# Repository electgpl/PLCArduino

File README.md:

# PLC Arduino NANO v1 

Este es un PLC de openHard diseñado en base al microcontrolador AVR linea MEGA compatible ArduinoIDE y ArduinoNANO

  - Core AVR - **ARDUINO NANO (Versión CH340)**
  - Bootloader UART Arduino Compatible
  - USB Programming firmware
  - USB Serial Terminal/Debug
  - 4 Salidas contacto seco doble inversora 12Vdc 24Vdc 220Vac
  - 4 Entradas Digitales optoacopladas 0-10V 0-12V 0-24V 
  - 3 Entradas Analógicas Aisladas de 0-10V
  - Fuente de alimentación integrada

## Lenguajes Compatibles

  - C
  - C++
  - Basic
  - Ensamblador
  - Ladder
  - y mas...
  
## Diseño y Desarrollo

> Diseñado en dos capas con componentes THT para facilitar
> la integración al alumno, el desarrollo del PCB en el hogar y mantener
> el menor costo posible.
>                           
> PCB creado en [PCBWay].
> Diseño realizado en [Eagle].

### Instalación

Todos los archivos se encuentran disponibles en este repositorio, diagramas, pcb, etc...

### Pendientes

 - Migración del hardware AVR MEGA Compatible.
 - Incorporación de nuevos puertos de comunicación CAN, 232, 485, ethernet, BT, WiFi (Requiere un PCB de mayores dimensiones, miltilayers y tecnología SMT)
 - Mejoras en inmunidad al ruido con incorporación de componentes dedicados, MOV, TVS, PLCC, EMC, BEADS CORE
 - Mejora en la performance de la fuente utilizando un DCDC Sepic o Buck/Boost
 - Aumento de canales de entrada y salida
 - Incorporación de entrada 4-20mA

License
----

MIT

**Free Software, Hell Yeah!**

[PCBWay]: <https://www.pcbway.com/>
[Eagle]: <https://www.autodesk.com/products/eagle/overview>

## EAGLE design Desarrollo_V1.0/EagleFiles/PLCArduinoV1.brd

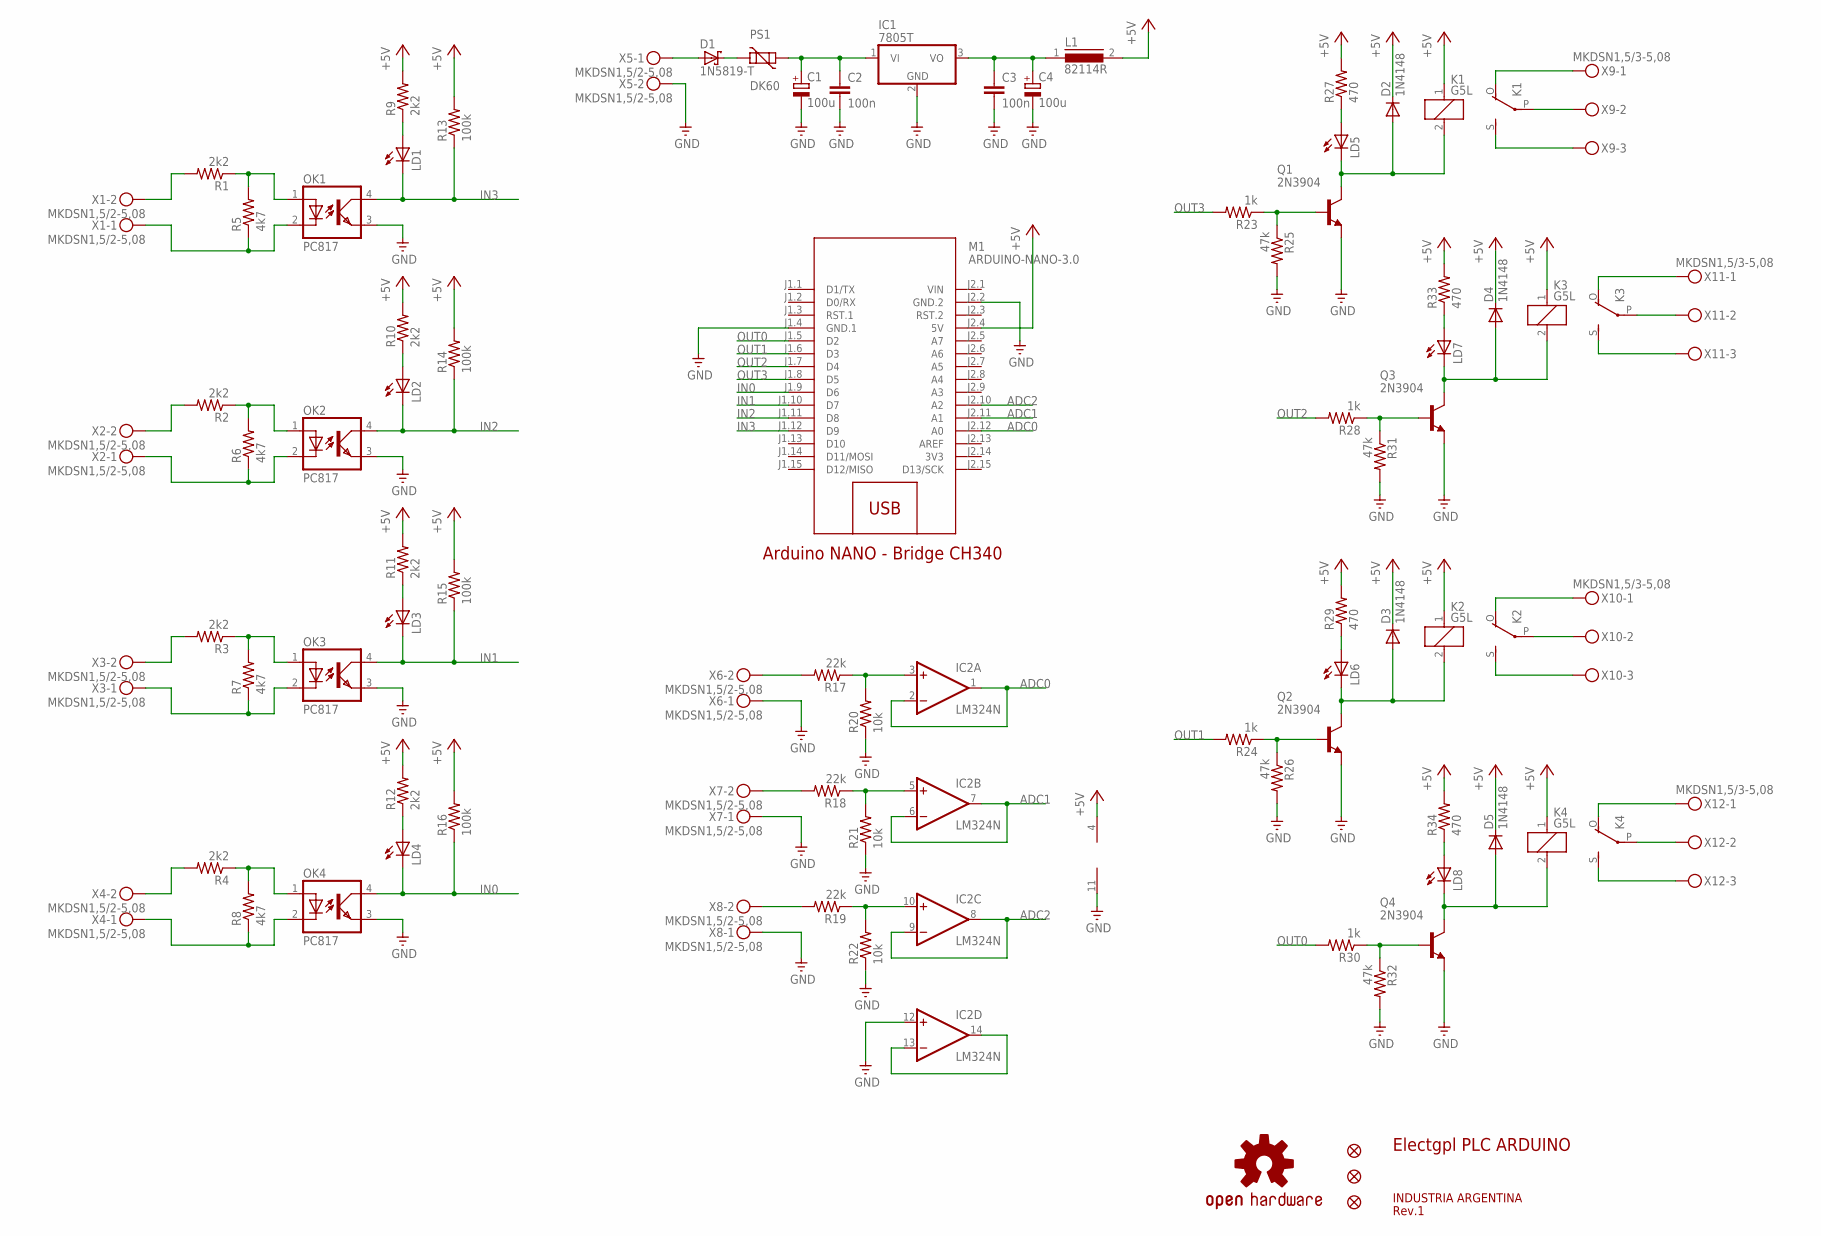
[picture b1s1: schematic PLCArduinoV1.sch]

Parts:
C1, C4: 100u; E3,5-8
C2, C3: 100n; C050-024X044
D1: 1N5819-T; DO41-7.6
D2, D3, D4, D5: 1N4148; DO35-10
IC1: 7805T; TO220H
IC2: LM324N; DIL14
JP1, JP2, JP3: FIDUCIAL1X2.5; FIDUCIAL-1X2.5
K1, K2, K3, K4: G5L; G5LE
L1: 82114R
LD1, LD2, LD3, LD4, LD5, LD6, LD7, LD8: LED3MM
M1: ARDUINO-NANO-3.0
OK1, OK2, OK3, OK4: PC817; DIL04
PS1: DK60; SO5K11
Q1, Q2, Q3, Q4: 2N3904; TO92
R1, R2, R3, R4, R9, R10, R11, R12: 2k2; 0204/5
R5, R6, R7, R8: 4k7; 0204/5
R13, R14, R15, R16: 100k; 0204/5
R17, R18, R19: 22k; 0204/5
R20, R21, R22: 10k; 0204/5
R23, R24, R28, R30: 1k; 0204/5
R25, R26, R31, R32: 47k; 0204/5
R27, R29, R33, R34: 470; 0204/5
U1: OSHW-LOGOM; OSHW-LOGO-M
X1, X2, X3, X4, X5, X6, X7, X8: MKDSN1,5/2-5,08
X9, X10, X11, X12: MKDSN1,5/3-5,08

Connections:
3V3: M1.J2.14 (3V3)
+5V: D2.C, D3.C, D4.C, D5.C, IC2.4 (V+), K1.1, K2.1, K3.1, K4.1, L1.2, M1.J2.4 (5V), R9.2, R10.2, R11.2, R12.2, R13.2, R14.2, R15.2, R16.2, R27.2, R29.2, R33.2, R34.2
ADC0: IC2.1 (OUT), IC2.2 (-IN), M1.J2.12 (A0)
ADC1: IC2.6 (-IN), IC2.7 (OUT), M1.J2.11 (A1)
ADC2: IC2.8 (OUT), IC2.9 (-IN), M1.J2.10 (A2)
GND: C1.-, C2.2, C3.2, C4.-, IC1.2 (GND), IC2.11 (V-), IC2.12 (+IN), M1.J1.4 (GND.1), M1.J2.2 (GND.2), OK1.3 (EMIT), OK2.3 (EMIT), OK3.3 (EMIT), OK4.3 (EMIT), Q1.3 (E), Q2.3 (E), Q3.3 (E), Q4.3 (E), R20.1, R21.1, R22.1, R25.2, R26.2, R31.2, R32.2, X5.2, X6.1, X7.1, X8.1
IN0: LD4.K (C), M1.J1.9 (D6), OK4.4 (COL), R16.1
IN1: LD3.K (C), M1.J1.10 (D7), OK3.4 (COL), R15.1
IN2: LD2.K (C), M1.J1.11 (D8), OK2.4 (COL), R14.1
IN3: LD1.K (C), M1.J1.12 (D9), OK1.4 (COL), R13.1
unnamed: LD5.A, R27.1
unnamed: D2.A, K1.2, LD5.K (C), Q1.1 (C)
unnamed: Q1.2 (B), R23.1, R25.1
unnamed: K1.P, X9.2
unnamed: K1.O, X9.1
unnamed: K1.S, X9.3
unnamed: LD7.A, R33.1
unnamed: D4.A, K3.2, LD7.K (C), Q3.1 (C)
unnamed: Q3.2 (B), R28.1, R31.1
unnamed: K3.P, X11.2
unnamed: K3.O, X11.1
unnamed: K3.S, X11.3
unnamed: LD6.A, R29.1
unnamed: D3.A, K2.2, LD6.K (C), Q2.1 (C)
unnamed: Q2.2 (B), R24.1, R26.1
unnamed: K2.P, X10.2
unnamed: K2.O, X10.1
unnamed: K2.S, X10.3
unnamed: LD8.A, R34.1
unnamed: D5.A, K4.2, LD8.K (C), Q4.1 (C)
unnamed: Q4.2 (B), R30.1, R32.1
unnamed: K4.P, X12.2
unnamed: K4.O, X12.1
unnamed: K4.S, X12.3
unnamed: OK1.1 (A), R1.1, R5.2
unnamed: OK1.2 (C), R5.1, X1.1
unnamed: R17.2, X6.2
unnamed: R18.2, X7.2
unnamed: LD1.A, R9.1
unnamed: R1.2, X1.2
unnamed: R19.2, X8.2
unnamed: OK2.1 (A), R2.1, R6.2
unnamed: OK2.2 (C), R6.1, X2.1
unnamed: LD2.A, R10.1
unnamed: R2.2, X2.2
unnamed: OK3.1 (A), R3.1, R7.2
unnamed: OK3.2 (C), R7.1, X3.1
unnamed: D1.A, X5.1
unnamed: LD3.A, R11.1
unnamed: R3.2, X3.2
unnamed: OK4.1 (A), R4.1, R8.2
unnamed: OK4.2 (C), R8.1, X4.1
unnamed: D1.C, PS1.2
unnamed: LD4.A, R12.1
unnamed: R4.2, X4.2
unnamed: C1.+, C2.1, IC1.1 (VI), PS1.1
unnamed: C3.1, C4.+, IC1.3 (VO), L1.1
unnamed: IC2.3 (+IN), R17.1, R20.2
unnamed: IC2.5 (+IN), R18.1, R21.2
unnamed: IC2.10 (+IN), R19.1, R22.2
unnamed: IC2.13 (-IN), IC2.14 (OUT)
OUT0: M1.J1.5 (D2), R30.2
OUT1: M1.J1.6 (D3), R24.2
OUT2: M1.J1.7 (D4), R28.2
OUT3: M1.J1.8 (D5), R23.2
VIN: M1.J2.1 (VIN)

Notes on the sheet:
Electgpl PLC ARDUINO
INDUSTRIA ARGENTINA
Rev.1
Arduino NANO - Bridge CH340

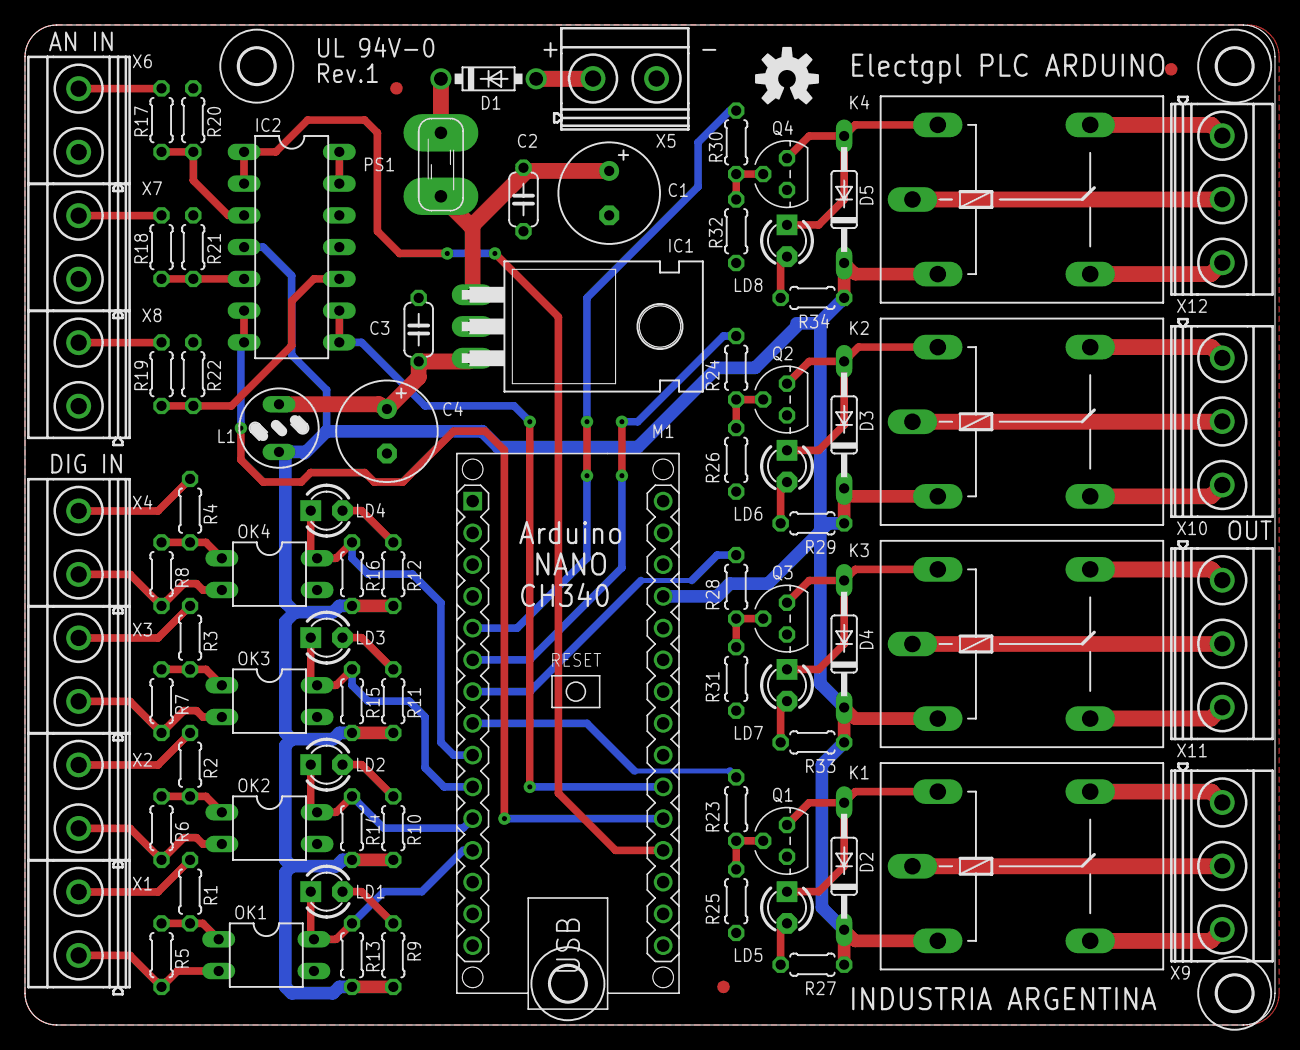
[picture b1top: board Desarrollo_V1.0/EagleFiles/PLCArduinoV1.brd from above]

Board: 2 copper layers, 100.0 x 80.0 mm, 88 parts (0 on the bottom side), 64 nets.

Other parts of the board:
U$2, U$3, U$4, U$5: 2,8

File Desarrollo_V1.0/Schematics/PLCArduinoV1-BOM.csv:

"Qty";"Value";"Device";"Package";"Parts";"Description";"SPICEPREFIX";
"8";"";"LED3MM";"LED3MM";"LD1, LD2, LD3, LD4, LD5, LD6, LD7, LD8";"LED";"";
"4";"100k";"R-US_0204/5";"0204/5";"R13, R14, R15, R16";"RESISTOR, American symbol";"R";
"2";"100n";"C-EU050-024X044";"C050-024X044";"C2, C3";"CAPACITOR, European symbol";"C";
"2";"100u";"CPOL-EUE3.5-8";"E3,5-8";"C1, C4";"POLARIZED CAPACITOR, European symbol";"C";
"3";"10k";"R-US_0204/5";"0204/5";"R20, R21, R22";"RESISTOR, American symbol";"R";
"4";"1N4148";"1N4148";"DO35-10";"D2, D3, D4, D5";"DIODE";"";
"1";"1N5819-T";"1N5819-T";"DO41-7.6";"D1";"1.0A SCHOTTKY BARRIER RECTIFIER";"";
"4";"1k";"R-US_0204/5";"0204/5";"R23, R24, R28, R30";"RESISTOR, American symbol";"R";
"3";"22k";"R-US_0204/5";"0204/5";"R17, R18, R19";"RESISTOR, American symbol";"R";
"4";"2N3904";"2N3904";"TO92";"Q1, Q2, Q3, Q4";"NPN Transistor";"";
"8";"2k2";"R-US_0204/5";"0204/5";"R1, R2, R3, R4, R9, R10, R11, R12";"RESISTOR, American symbol";"R";
"4";"470";"R-US_0204/5";"0204/5";"R27, R29, R33, R34";"RESISTOR, American symbol";"R";
"4";"47k";"R-US_0204/5";"0204/5";"R25, R26, R31, R32";"RESISTOR, American symbol";"R";
"4";"4k7";"R-US_0204/5";"0204/5";"R5, R6, R7, R8";"RESISTOR, American symbol";"R";
"1";"7805T";"7805T";"TO220H";"IC1";"Positive VOLTAGE REGULATOR";"";
"1";"82114R";"82114R";"82114R";"L1";"INDUCTOR";"L";
"1";"ARDUINO-NANO-3.0";"ARDUINO-NANO-3.0";"ARDUINO-NANO-3.0";"M1";"Arduino Nano 3.0 and compatible devices";"";
"1";"DK60";"POLYSWITCH5MM";"SO5K11";"PS1";"";"";
"3";"FIDUCIAL1X2.5";"FIDUCIAL1X2.5";"FIDUCIAL-1X2.5";"JP1, JP2, JP3";"Fiducial Alignment Points";"";
"4";"G5L";"G5L";"G5LE";"K1, K2, K3, K4";"RELAY";"";
"1";"LM324N";"LM324N";"DIL14";"IC2";"OP AMP";"";
"8";"MKDSN1,5/2-5,08";"MKDSN1,5/2-5,08";"MKDSN1,5/2-5,08";"X1, X2, X3, X4, X5, X6, X7, X8";"MKDSN 1,5/ 2-5,08 Printklemme";"";
"4";"MKDSN1,5/3-5,08";"MKDSN1,5/3-5,08";"MKDSN1,5/3-5,08";"X9, X10, X11, X12";"MKDSN 1,5/ 3-5,08 Printklemme";"";
"1";"OSHW-LOGOM";"OSHW-LOGOM";"OSHW-LOGO-M";"U1";"Open Source Hardware Logo This logo indicates the piece of hardware it is found on incorporates a OSHW license and/or adheres to the definition of open source hardware found here: http://freedomdefined.org/OSHW";"";
"4";"PC817";"PC817";"DIL04";"OK1, OK2, OK3, OK4";"SHARP OPTO COUPLER";"";

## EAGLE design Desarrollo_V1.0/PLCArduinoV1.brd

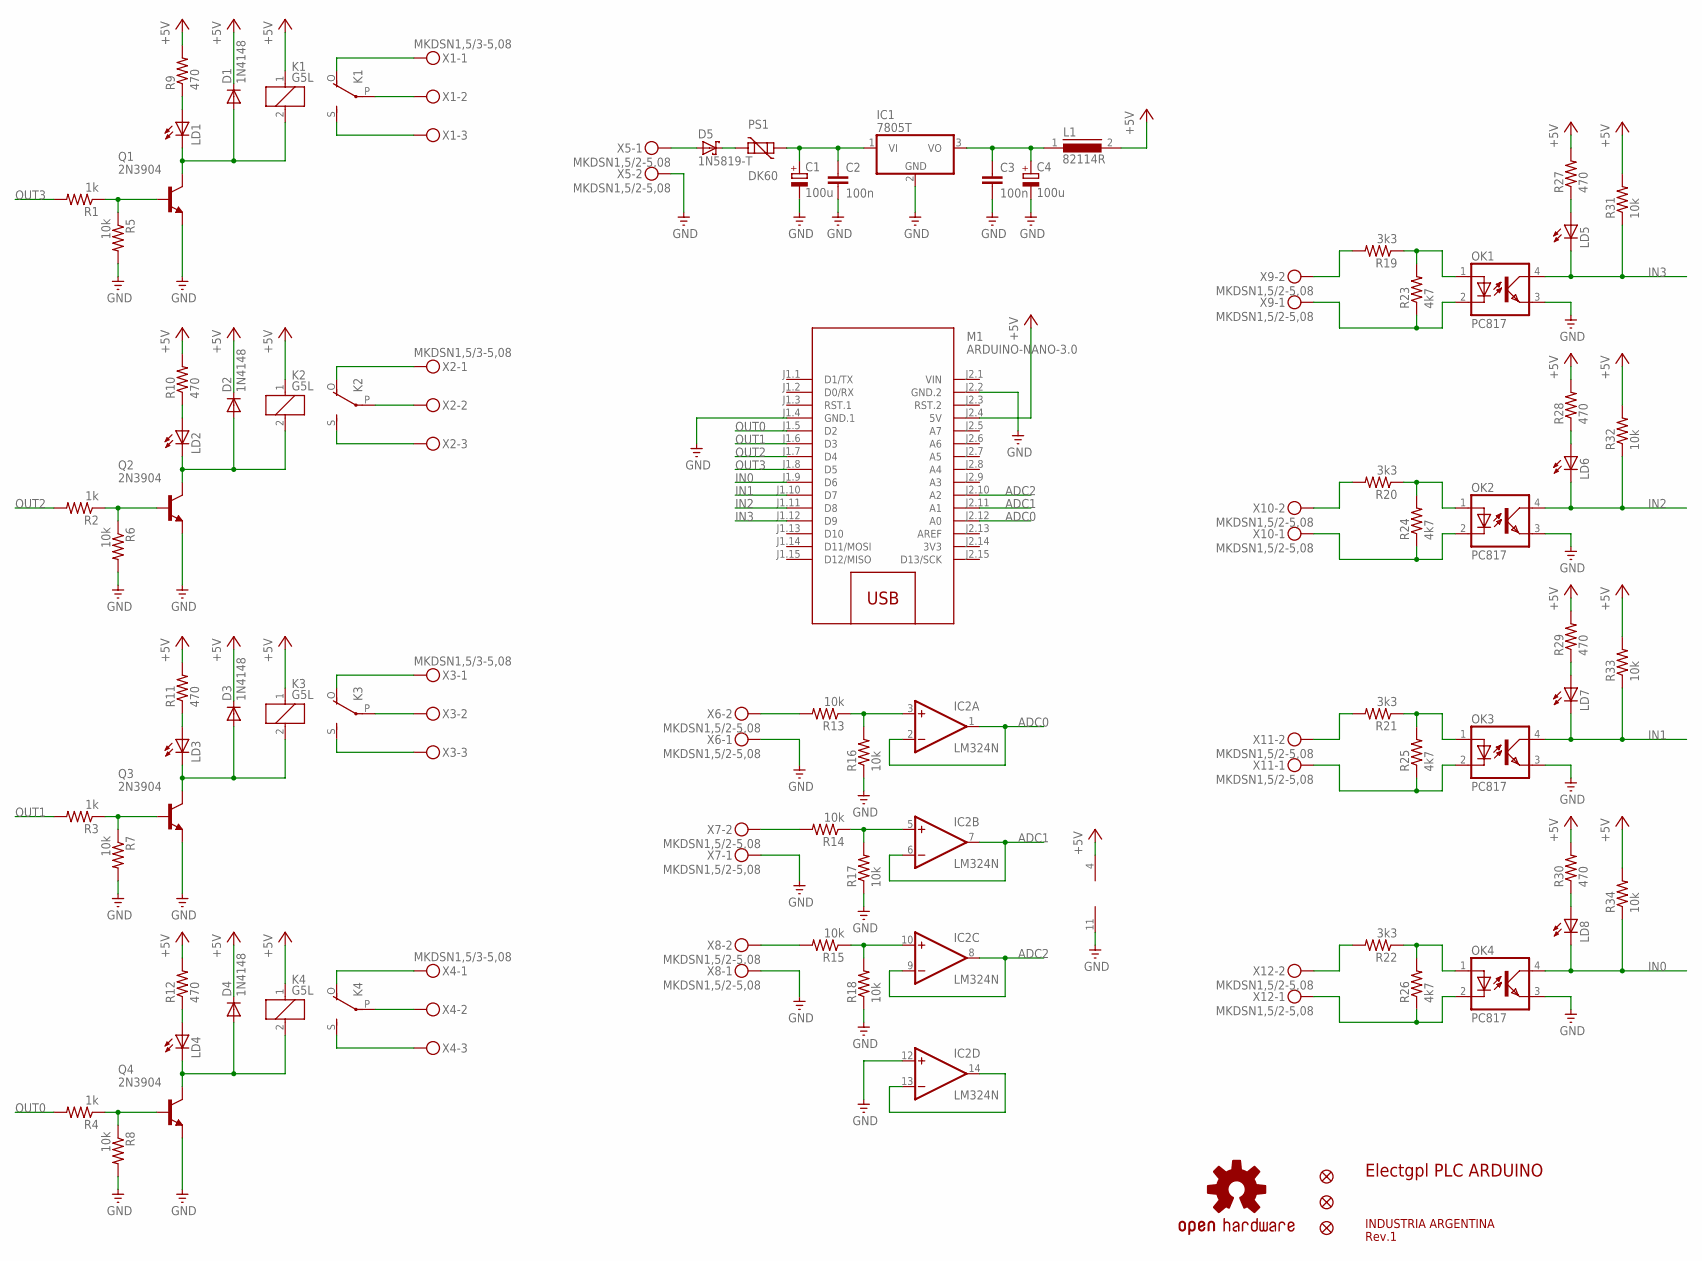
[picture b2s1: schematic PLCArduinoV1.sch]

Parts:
C1, C4: 100u; E3,5-8
C2, C3: 100n; C050-024X044
D1, D2, D3, D4: 1N4148; DO35-10
D5: 1N5819-T; DO41-7.6
IC1: 7805T; TO220H
IC2: LM324N; DIL14
JP1, JP2, JP3: FIDUCIAL1X2.5; FIDUCIAL-1X2.5
K1, K2, K3, K4: G5L; G5LE
L1: 82114R
LD1, LD2, LD3, LD4, LD5, LD6, LD7, LD8: LED3MM
M1: ARDUINO-NANO-3.0
OK1, OK2, OK3, OK4: PC817; DIL04
PS1: DK60; SO5K11
Q1, Q2, Q3, Q4: 2N3904; TO92
R1, R2, R3, R4: 1k; 0204/5
R5, R6, R7, R8, R13, R14, R15, R16, R17, R18, R31, R32, R33, R34: 10k; 0204/5
R9, R10, R11, R12, R27, R28, R29, R30: 470; 0204/5
R19, R20, R21, R22: 3k3; 0204/5
R23, R24, R25, R26: 4k7; 0204/5
U1: OSHW-LOGOM; OSHW-LOGO-M
X1, X2, X3, X4: MKDSN1,5/3-5,08
X5, X6, X7, X8, X9, X10, X11, X12: MKDSN1,5/2-5,08

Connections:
3V3: M1.J2.14 (3V3)
+5V: D1.C, D2.C, D3.C, D4.C, IC2.4 (V+), K1.1, K2.1, K3.1, K4.1, L1.2, M1.J2.4 (5V), R9.2, R10.2, R11.2, R12.2, R27.2, R28.2, R29.2, R30.2, R31.2, R32.2, R33.2, R34.2
ADC0: IC2.1 (OUT), IC2.2 (-IN), M1.J2.12 (A0)
ADC1: IC2.6 (-IN), IC2.7 (OUT), M1.J2.11 (A1)
ADC2: IC2.8 (OUT), IC2.9 (-IN), M1.J2.10 (A2)
GND: C1.-, C2.2, C3.2, C4.-, IC1.2 (GND), IC2.11 (V-), IC2.12 (+IN), M1.J1.4 (GND.1), M1.J2.2 (GND.2), OK1.3 (EMIT), OK2.3 (EMIT), OK3.3 (EMIT), OK4.3 (EMIT), Q1.3 (E), Q2.3 (E), Q3.3 (E), Q4.3 (E), R5.2, R6.2, R7.2, R8.2, R16.1, R17.1, R18.1, X5.2, X6.1, X7.1, X8.1
IN0: LD8.K (C), M1.J1.9 (D6), OK4.4 (COL), R34.1
IN1: LD7.K (C), M1.J1.10 (D7), OK3.4 (COL), R33.1
IN2: LD6.K (C), M1.J1.11 (D8), OK2.4 (COL), R32.1
IN3: LD5.K (C), M1.J1.12 (D9), OK1.4 (COL), R31.1
unnamed: LD1.A, R9.1
unnamed: D1.A, K1.2, LD1.K (C), Q1.1 (C)
unnamed: Q1.2 (B), R1.1, R5.1
unnamed: K1.P, X1.2
unnamed: K1.O, X1.1
unnamed: K1.S, X1.3
unnamed: LD2.A, R10.1
unnamed: D2.A, K2.2, LD2.K (C), Q2.1 (C)
unnamed: Q2.2 (B), R2.1, R6.1
unnamed: K2.P, X2.2
unnamed: K2.O, X2.1
unnamed: K2.S, X2.3
unnamed: LD3.A, R11.1
unnamed: D3.A, K3.2, LD3.K (C), Q3.1 (C)
unnamed: Q3.2 (B), R3.1, R7.1
unnamed: K3.P, X3.2
unnamed: K3.O, X3.1
unnamed: K3.S, X3.3
unnamed: LD4.A, R12.1
unnamed: D4.A, K4.2, LD4.K (C), Q4.1 (C)
unnamed: Q4.2 (B), R4.1, R8.1
unnamed: K4.P, X4.2
unnamed: K4.O, X4.1
unnamed: K4.S, X4.3
unnamed: OK1.1 (A), R19.1, R23.2
unnamed: OK1.2 (C), R23.1, X9.1
unnamed: R13.2, X6.2
unnamed: R14.2, X7.2
unnamed: LD5.A, R27.1
unnamed: R19.2, X9.2
unnamed: R15.2, X8.2
unnamed: OK2.1 (A), R20.1, R24.2
unnamed: OK2.2 (C), R24.1, X10.1
unnamed: LD6.A, R28.1
unnamed: R20.2, X10.2
unnamed: OK3.1 (A), R21.1, R25.2
unnamed: OK3.2 (C), R25.1, X11.1
unnamed: D5.A, X5.1
unnamed: LD7.A, R29.1
unnamed: R21.2, X11.2
unnamed: OK4.1 (A), R22.1, R26.2
unnamed: OK4.2 (C), R26.1, X12.1
unnamed: D5.C, PS1.2
unnamed: LD8.A, R30.1
unnamed: R22.2, X12.2
unnamed: C1.+, C2.1, IC1.1 (VI), PS1.1
unnamed: C3.1, C4.+, IC1.3 (VO), L1.1
unnamed: IC2.3 (+IN), R13.1, R16.2
unnamed: IC2.5 (+IN), R14.1, R17.2
unnamed: IC2.10 (+IN), R15.1, R18.2
unnamed: IC2.13 (-IN), IC2.14 (OUT)
OUT0: M1.J1.5 (D2), R4.2
OUT1: M1.J1.6 (D3), R3.2
OUT2: M1.J1.7 (D4), R2.2
OUT3: M1.J1.8 (D5), R1.2
VIN: M1.J2.1 (VIN)

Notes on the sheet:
Electgpl PLC ARDUINO
INDUSTRIA ARGENTINA
Rev.1

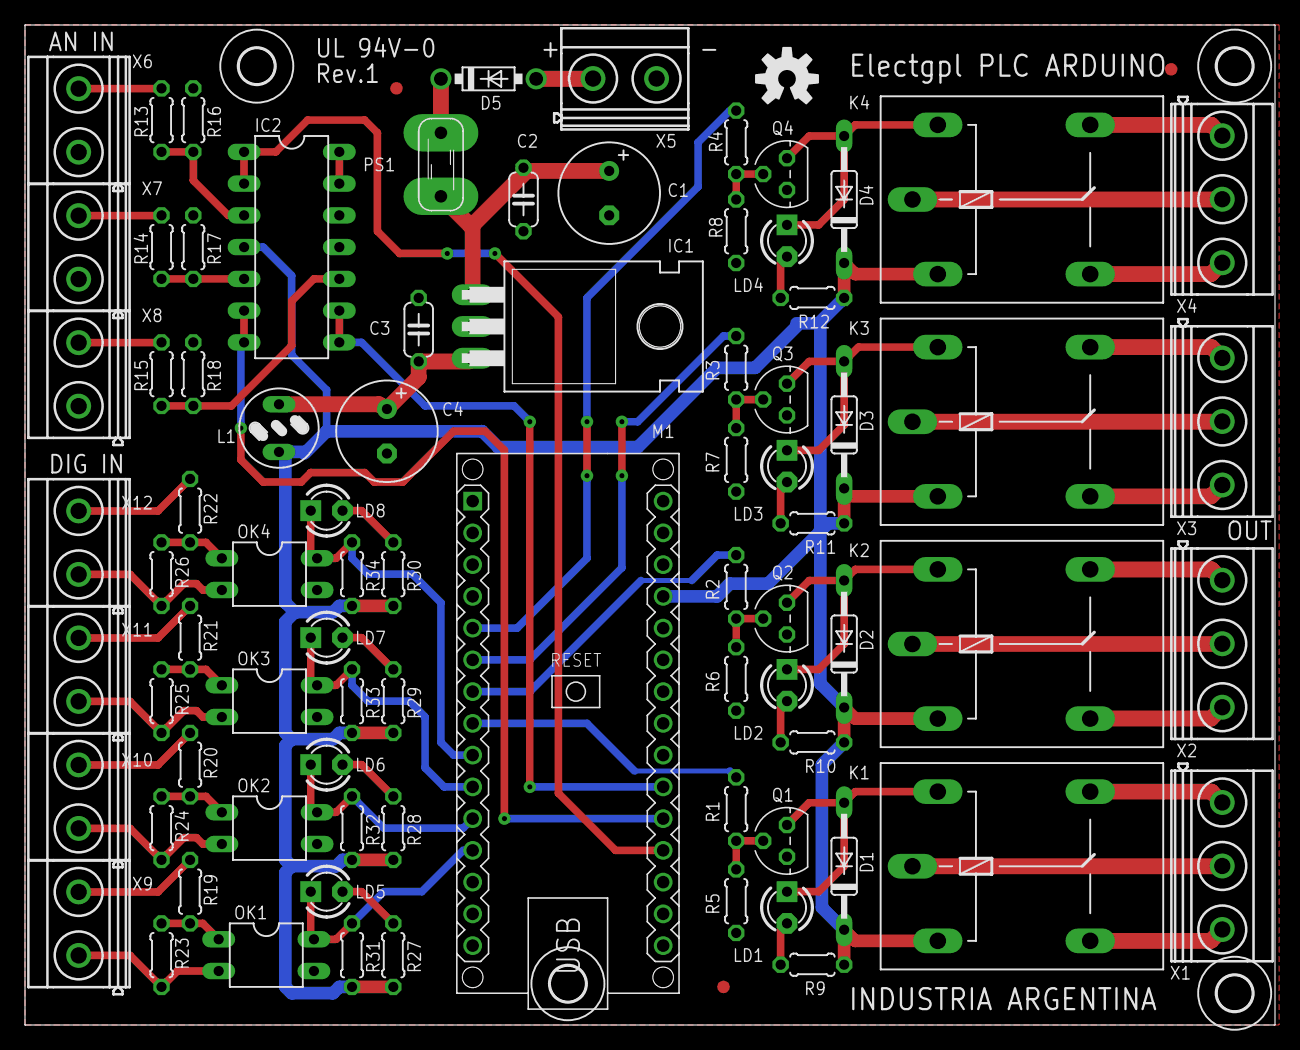
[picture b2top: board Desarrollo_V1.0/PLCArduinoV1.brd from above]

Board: 2 copper layers, 100.0 x 80.0 mm, 88 parts (0 on the bottom side), 64 nets.

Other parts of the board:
U$2, U$3, U$4, U$5: 2,8

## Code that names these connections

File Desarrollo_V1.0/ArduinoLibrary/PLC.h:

/* Copyright 2018, Sebastian Caccavallo
 *
 * Todos los derechos reservados.
 *
 * Este archivo es parte de la biblioteca PLC 344 rev.1.0 para Arduino.
 *
 * Redistribución y uso en formas fuente y binarias, con o sin modificación,
 * están permitidos siempre que se cumplan las siguientes condiciones:
 *
 * 1. Las redistribuciones del código fuente deben conservar el aviso de copyright 
 * anterior, esta lista de condiciones y el siguiente descargo de responsabilidad.
 *
 * 2. Las redistribuciones en formato binario deben reproducir el aviso de copyright 
 * anterior, esta lista de condiciones y la siguiente exención de responsabilidad en 
 * la documentación y / u otros materiales proporcionados con la distribución.
 *
 * 3. Ni el nombre del titular de los derechos de autor ni los nombres de sus
 * los contribuyentes pueden ser utilizados para respaldar o promocionar productos 
 * derivados de este software sin permiso escrito previo específico.
 *
 * ESTE SOFTWARE ES PROPORCIONADO POR LOS TITULARES DE LOS DERECHOS DE AUTOR Y LOS 
 * COLABORADORES "TAL CUAL" Y CUALQUIER GARANTÍA EXPRESA O IMPLÍCITA, INCLUIDAS, ENTRE OTRAS, 
 * LAS GARANTÍAS IMPLÍCITAS DE COMERCIABILIDAD E IDONEIDAD PARA UN PROPÓSITO EN PARTICULAR
 * SON RECHAZADOS. EN NINGÚN CASO SERÁ EL TITULAR DEL COPYRIGHT O LOS COLABORADORES
 * RESPONSABLE POR CUALQUIER DIRECTO, INDIRECTO, INCIDENTAL, ESPECIAL, EJEMPLAR O
 * DAÑOS CONSECUENTES (INCLUIDOS, ENTRE OTROS, LA ADQUISICIÓN DE
 * SUSTITUIR BIENES O SERVICIOS; PÉRDIDA DE USO, DATOS O GANANCIAS; O NEGOCIO
 * INTERRUPCIÓN) SIN EMBARGO Y EN CUALQUIER TEORÍA DE RESPONSABILIDAD, YA SEA EN
 * CONTRATO, RESPONSABILIDAD ESTRICTA O AGRAVIO (INCLUYENDO NEGLIGENCIA O DE OTRO TIPO)
 * QUE SURGE DE ALGUNA MANERA DEL USO DE ESTE SOFTWARE, AUN SI SE ACONSEJA
 * POSIBILIDAD DE DICHO DAÑO.
 *
 * Date: 2018-04-10 */

/*==================[inclusions]=============================================*/
#include "Arduino.h"
/*==================[macros and definitions]=================================*/
#define   Out1  2
#define   Out2  3
#define   Out3  4
#define   Out4  5

#define   In1   6
#define   In2   7
#define   In3   8
#define   In4   9

#define   An1   A0 
#define   An2   A1 
#define   An3   A2 

#define   Stat  13
/*==================[Data declaration]=======================================*/
typedef enum {
    ANALOG_IN_1 = A0,
    ANALOG_IN_2 = A1,
    ANALOG_IN_3 = A2
} PLCAnalogInput_t;

typedef enum {
    DIGITAL_IN_1 = 6,
    DIGITAL_IN_2 = 7,
    DIGITAL_IN_3 = 8,
    DIGITAL_IN_4 = 9
} PLCDigitalInput_t;

typedef enum {
    DIGITAL_OUT_1 = 2,
    DIGITAL_OUT_2 = 3,
    DIGITAL_OUT_3 = 4,
    DIGITAL_OUT_4 = 5
} PLCDigitalOutput_t;
/*==================[functions declaration]==================================*/
void PLC_Setup(void);

int PLC_ReadAnalogInputRaw(PLCAnalogInput_t input);

float PLC_ReadAnalogInputVolt(PLCAnalogInput_t input);

bool PLC_ReadContact(PLCDigitalInput_t input);

void PLC_WriteRelay(PLCDigitalOutput_t output, bool value);
/*==================[Data definition]========================================*/
/*==================[Functions definition]===================================*/

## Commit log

2018-03-16 test
2018-04-12 Add files via upload
    Se agregan funciones al ejemplo: Parada de Emergencia por sobre tensión
2018-04-12 Add files via upload
    Se agrega función RAW para los canales ADC. PLC_ReadAnalogInputRaw();

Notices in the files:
parts and their libraries:
diy-modules: Released under the Creative Commons Attribution 4.0 International License: http://creativecommons.org/licenses/by/4.0
SparkFun: Licensing: CC v3.0 Share-Alike You are welcome to use this library for commercial purposes.
